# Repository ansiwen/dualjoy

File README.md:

# DualJoy

This is a firmware for the Rapsberry Pi Pico that turns it into a USB adapter
for _two_ D-Sub 9 joysticks, as they where used for example with the Atari 2600
console and the Commodore C64 and Amiga home computers. They will appear as two
digital hats/d-pads with only one button.

The code is based on the various examples of the Pico SDK and TinyUSB and keeps
their MIT license.

## Usage

You can use the precompiled binary from the release page if you use the same
GPIOs as in the hardware example below:

GPIO | D-SUB pin | Function
-:|:-|:-
10 | 1 (J1) | J1 UP
11 | 2 (J1) | J1 DOWN
12 | 3 (J1) | J1 LEFT
13 | 4 (J1) | J1 RIGHT
9 | 6 (J1) | J1 BTN
18 | 1 (J2) | J2 UP
19 | 2 (J2) | J2 DOWN
20 | 3 (J2) | J2 LEFT
21 | 4 (J2) | J2 RIGHT
17 | 6 (J2) | J2 BTN

Additionally you need to connect pin 8 of both D-SUB connectors with GND on the
Pico.

## Build

If you want to use different GPIOs, you easily can build the firmware yourself.
Like any other pico project, after installing the
[Pico SDK](https://github.com/raspberrypi/pico-sdk) you do:

```
$ mkdir build
$ cd build
$ cmake ..
$ make
```

If building for the Pico 2 (RP2350), use `cmake -DPICO_BOARD=pico2 ..` instead.

## Simple hardware example

<p align="justify">

  &nbsp;&nbsp;&nbsp;&nbsp;&nbsp;&nbsp;&nbsp;&nbsp;&nbsp;&nbsp;
</p>

## PCB

A ready-made PCB with a matching top and bottom plate as enclosure is available
in [hardware/](hardware/README.md).

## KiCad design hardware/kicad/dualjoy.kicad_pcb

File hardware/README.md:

# DualJoy PCB

A PCB for the DualJoy firmware: a Raspberry Pi Pico and two D-SUB 9
connectors on one board, sandwiched between a top and a bottom plate that act
as a simple enclosure. The top plate carries the DualJoy logo in silkscreen.

The design consists of three boards:

Board | Description
:-|:-
Main board | Pico and the two D-SUB connectors
Top plate | Cover with the DualJoy logo
Bottom plate | Plain cover

Renders of the main board:

Renders of the top plate:

## Wiring

The main board uses the same GPIOs as the [firmware](../README.md#usage), so
the precompiled binary works without changes:

GPIO | D-SUB pin | Function
-:|:-|:-
10 | 1 (J1) | J1 UP
11 | 2 (J1) | J1 DOWN
12 | 3 (J1) | J1 LEFT
13 | 4 (J1) | J1 RIGHT
9 | 6 (J1) | J1 BTN
18 | 1 (J2) | J2 UP
19 | 2 (J2) | J2 DOWN
20 | 3 (J2) | J2 LEFT
21 | 4 (J2) | J2 RIGHT
17 | 6 (J2) | J2 BTN
GND | 8 (J1, J2) | GND

The schematic is available as [PDF](docs/dualjoy.pdf).

## Files

Path | Content
:-|:-
[`kicad/`](kicad/) | KiCad projects for all three boards (requires KiCad 10 or newer)
[`gerbers/`](gerbers/) | Gerber and drill files, one zip per board, ready to upload to a PCB fab
[`docs/`](docs/) | Schematic as PDF
[`images/`](images/) | Photos and renders

## Ordering

The boards were made by [JLCPCB](https://jlcpcb.com/). Upload each zip from
[`gerbers/`](gerbers/) as a separate order. Apart from the colour, the
standard options are fine: FR-4, 2 layers, 1.6 mm, 1 oz copper, HASL. All
three boards measure 66.45 × 55.98 mm.

Optionally choose "Remove Mark" under "Mark on PCB", so JLCPCB doesn't print
its order number on the board.

Board | Gerber file | Colour used
:-|:-|:-
Main board | `dualjoy-pcb-v1.0.zip` | white, black silkscreen
Top plate | `dualjoy-top-plate-v1.0.zip` | black or red, white silkscreen
Bottom plate | `dualjoy-bottom-plate-v1.0.zip` | black or red, white silkscreen

## Bill of materials

Qty | Part | Note
-:|:-|:-
1 | Raspberry Pi Pico or Pico 2 | soldered directly or with pin headers
2 | D-SUB 9 male connector, right angle, PCB mount | J1, J2, see below
4 | M3 × 15 mm standoff, female–female | between top plate and main board
4 | M3 × 6 mm standoff, female–female | between main board and bottom plate
4 | M3 × 6 mm screw | through the top plate
4 | M3 × 12 mm screw | through the bottom plate and main board

Any right-angle D-SUB 9 male connector with the standard PCB layout fits:
pitch 2.77 × 2.84 mm and two mounting holes 25 mm apart, centered between the
pin rows. These two have been used, both with a 9.4 mm footprint:

- [D-SUB ST 09EU](https://www.reichelt.de/de/de/shop/produkt/d-sub-stecker_9-polig_gewinkelt_rm_9_4-6986)
  (Reichelt), with 4-40 UNC screw locks fitted
- [W+P 107-09-1-1-0](https://www.reichelt.de/de/de/shop/produkt/d-sub_stecker_9-polig_gewinkelt-293990)
  (Reichelt), without screw locks

The standoffs and screws used are nylon, from an M3 assortment kit
([white](https://www.amazon.de/dp/B0DCS43SSC),
[black](https://www.amazon.de/dp/B09C21MS45)).

## Assembly

1. Solder the Pico and the two D-SUB connectors onto the main board. The Pico
   footprint supports both soldering the Pico directly onto the board and
   mounting it with pin headers soldered to the Pico first.
2. Flash the [DualJoy firmware](../README.md) onto the Pico.
3. Assemble the sandwich at each of the four corners, from top to bottom:
   - M3 × 6 mm screw through the top plate
   - M3 × 15 mm standoff
   - main board
   - M3 × 6 mm standoff
   - bottom plate, with the M3 × 12 mm screw from below through the bottom
     plate, the short standoff and the main board into the long standoff

The board has been built and tested with both the Raspberry Pi Pico and the
Pico 2, using the firmware from the main [README](../README.md#build).

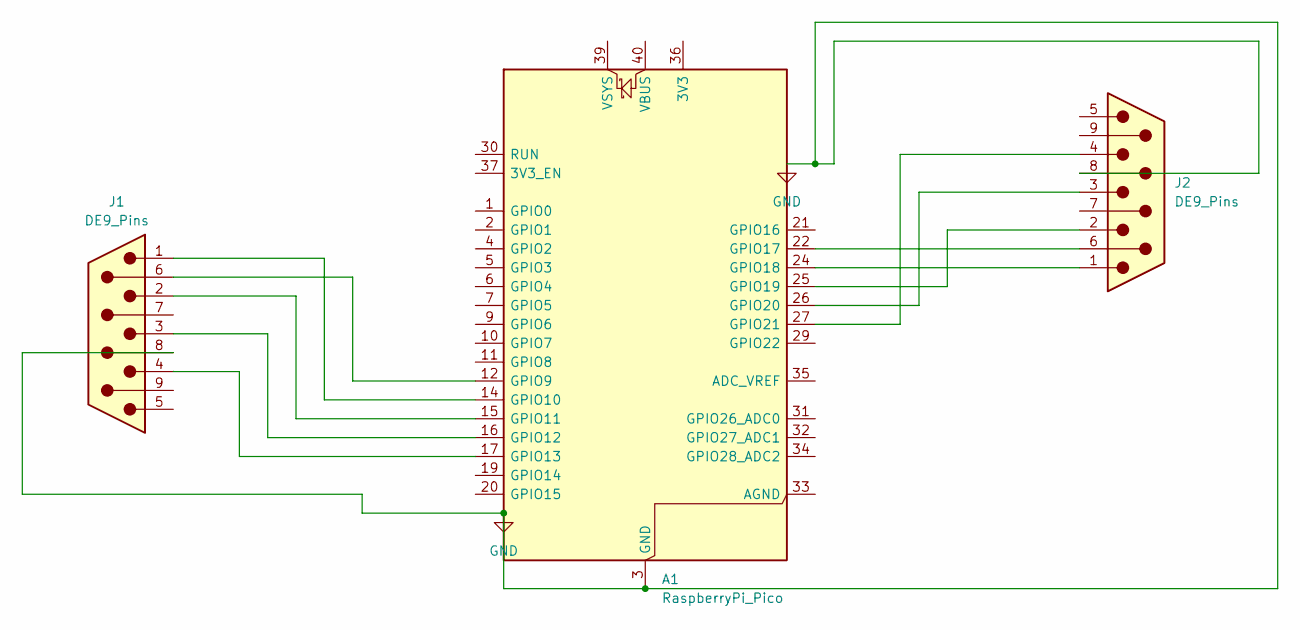
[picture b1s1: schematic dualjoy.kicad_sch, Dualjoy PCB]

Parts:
A1: RaspberryPi_Pico; RaspberryPi_Pico_Common_Unspecified
J1, J2: DE9_Pins; DSUB-9_Pins_Horizontal_P2.77x2.84mm_EdgePinOffset9.90mm_Hou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

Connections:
GND: A1.3 (GND), A1.8 (GND), A1.13 (GND), A1.18 (GND), A1.23 (GND), A1.28 (GND), A1.38 (GND), J1.8, J2.8
unnamed: A1.12 (GPIO9), J1.6
unnamed: A1.14 (GPIO10), J1.1
unnamed: A1.15 (GPIO11), J1.2
unnamed: A1.16 (GPIO12), J1.3
unnamed: A1.17 (GPIO13), J1.4
unnamed: A1.22 (GPIO17), J2.6
unnamed: A1.24 (GPIO18), J2.1
unnamed: A1.25 (GPIO19), J2.2
unnamed: A1.26 (GPIO20), J2.3
unnamed: A1.27 (GPIO21), J2.4

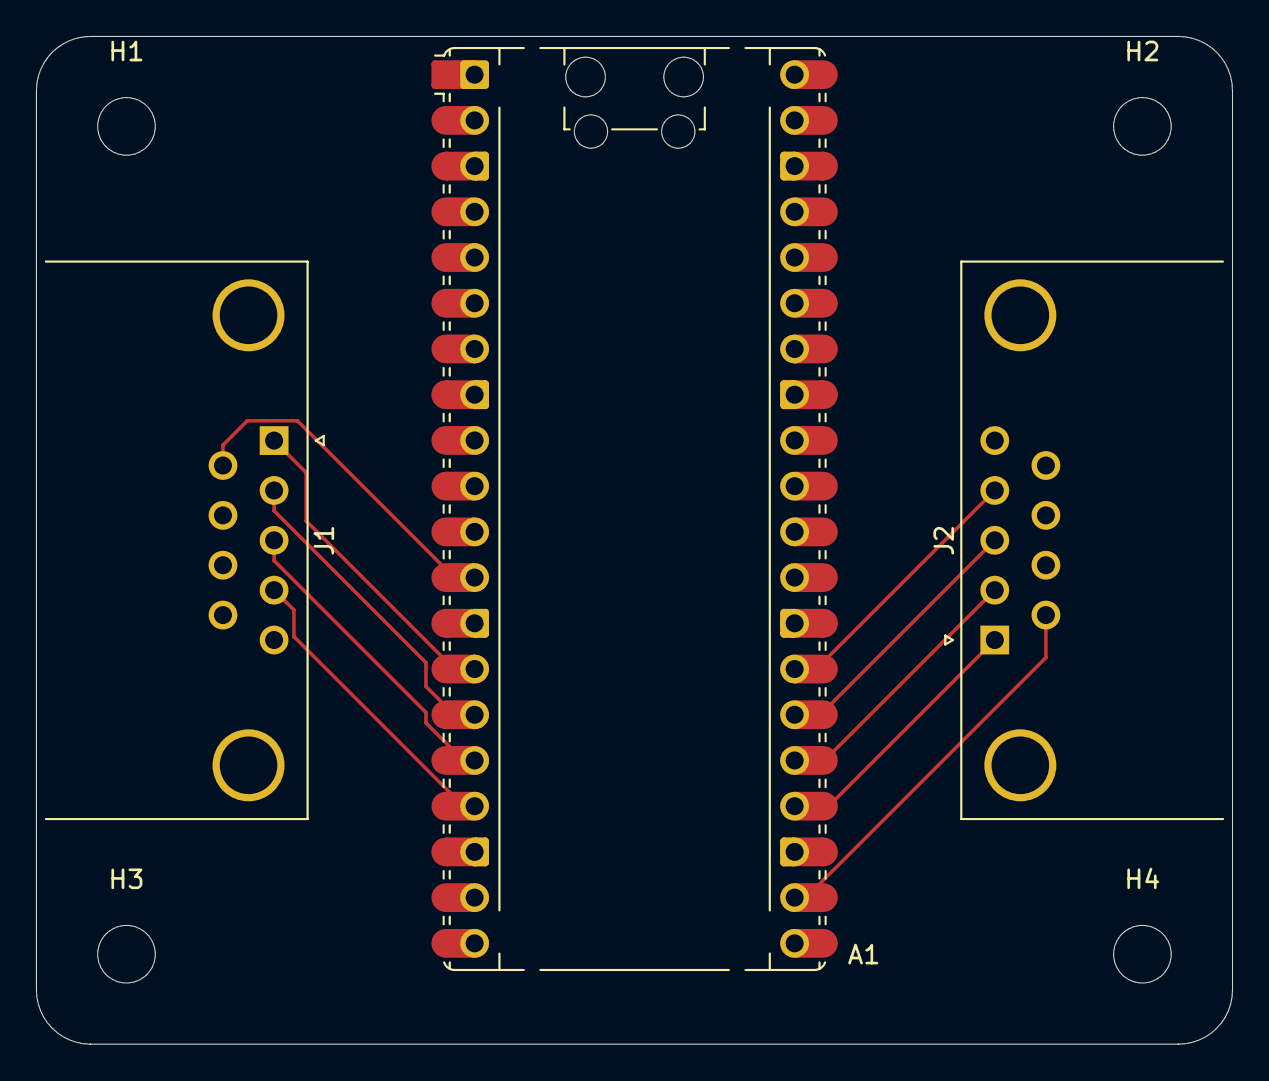
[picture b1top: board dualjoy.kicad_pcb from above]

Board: 2 copper layers, 66.4 x 56.0 mm, 7 parts (0 on the bottom side), 11 nets.

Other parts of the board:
H1, H2, H3, H4: MountingHole_3.2mm_M3

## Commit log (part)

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2025-01-04 Initial implementation based on GPIO IRQs
2025-01-04 Make refinements
2025-01-06 Implement new HAT based version
2025-01-06 Improve state handling with state bitmap
2025-01-06 Do some chores
2025-01-07 Do more refinements
2025-01-13 Minor cleanup
2026-02-27 make report descriptor more conventional
2026-02-27 add RP2350 support
